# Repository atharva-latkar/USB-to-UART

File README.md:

# USB-to-UART

A compact, custom-designed USB-to-UART converter PCB based on the CH340G USB-to-Serial IC. This project converts USB communication into UART serial signals, making it useful for programming, debugging, and serial communication with microcontrollers and embedded systems.

# Project Preview

# Features

1. USB Type-A interface for connecting to a computer.
2. CH340G USB-to-UART bridge IC.
3. UART TX and RX communication interface.
4. 4-pin output header for easy connectivity.
5. External crystal oscillator circuit.
6. Dedicated mounting holes for PCB installation.
7. Custom-designed schematic and PCB layout.

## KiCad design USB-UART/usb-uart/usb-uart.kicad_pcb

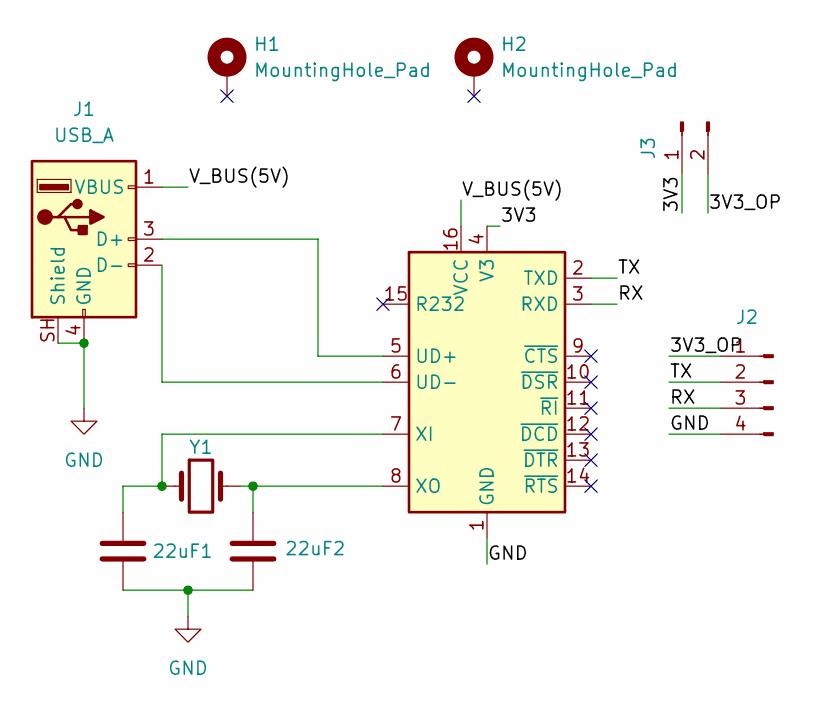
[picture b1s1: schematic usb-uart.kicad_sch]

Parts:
22uF1, 22uF2: C; C_01005_0402Metric
H1, H2: MountingHole_Pad; MountingHole_2.2mm_M2_DIN965_Pad
J1: USB_A; USB_A_CNCTech_1001-011-01101_Horizontal
J2: Conn_01x04_Pin; FanPinHeader_1x04_P2.54mm_Vertical
J3: Conn_01x02_Pin; PinHeader_1x02_P2.54mm_Vertical
U1: CH340G; SOIC-16_3.9x9.9mm_P1.27mm
Y1: Crystal; Crystal_HC49-U_Horizontal

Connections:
/3V3: J3.1, U1.4 (V3)
/3V3_OP: J2.1, J3.2
/RX: J2.3, U1.3 (RXD)
/TX: J2.2, U1.2 (TXD)
/V_BUS(5V): J1.1 (VBUS), U1.16 (VCC)
GND: 22uF1.2, 22uF2.2, J1.4 (GND), J1.SH (Shield), J2.4, U1.1 (GND)
unnamed: J1.3 (D+), U1.5 (UD+)
unnamed: J1.2 (D-), U1.6 (UD-)
unnamed: 22uF1.1, U1.7 (XI), Y1.1
unnamed: 22uF2.1, U1.8 (XO), Y1.2

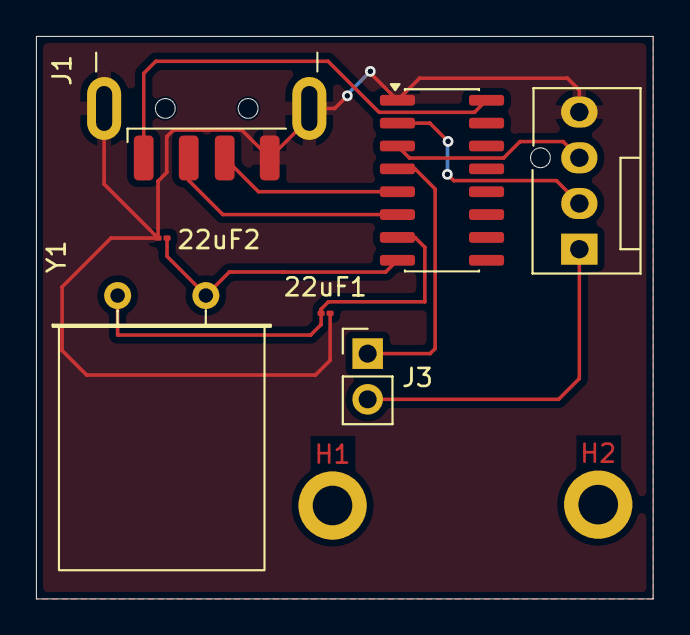
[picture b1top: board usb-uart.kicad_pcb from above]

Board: 2 copper layers, 34.3 x 31.2 mm, 9 parts (0 on the bottom side), 10 nets.
